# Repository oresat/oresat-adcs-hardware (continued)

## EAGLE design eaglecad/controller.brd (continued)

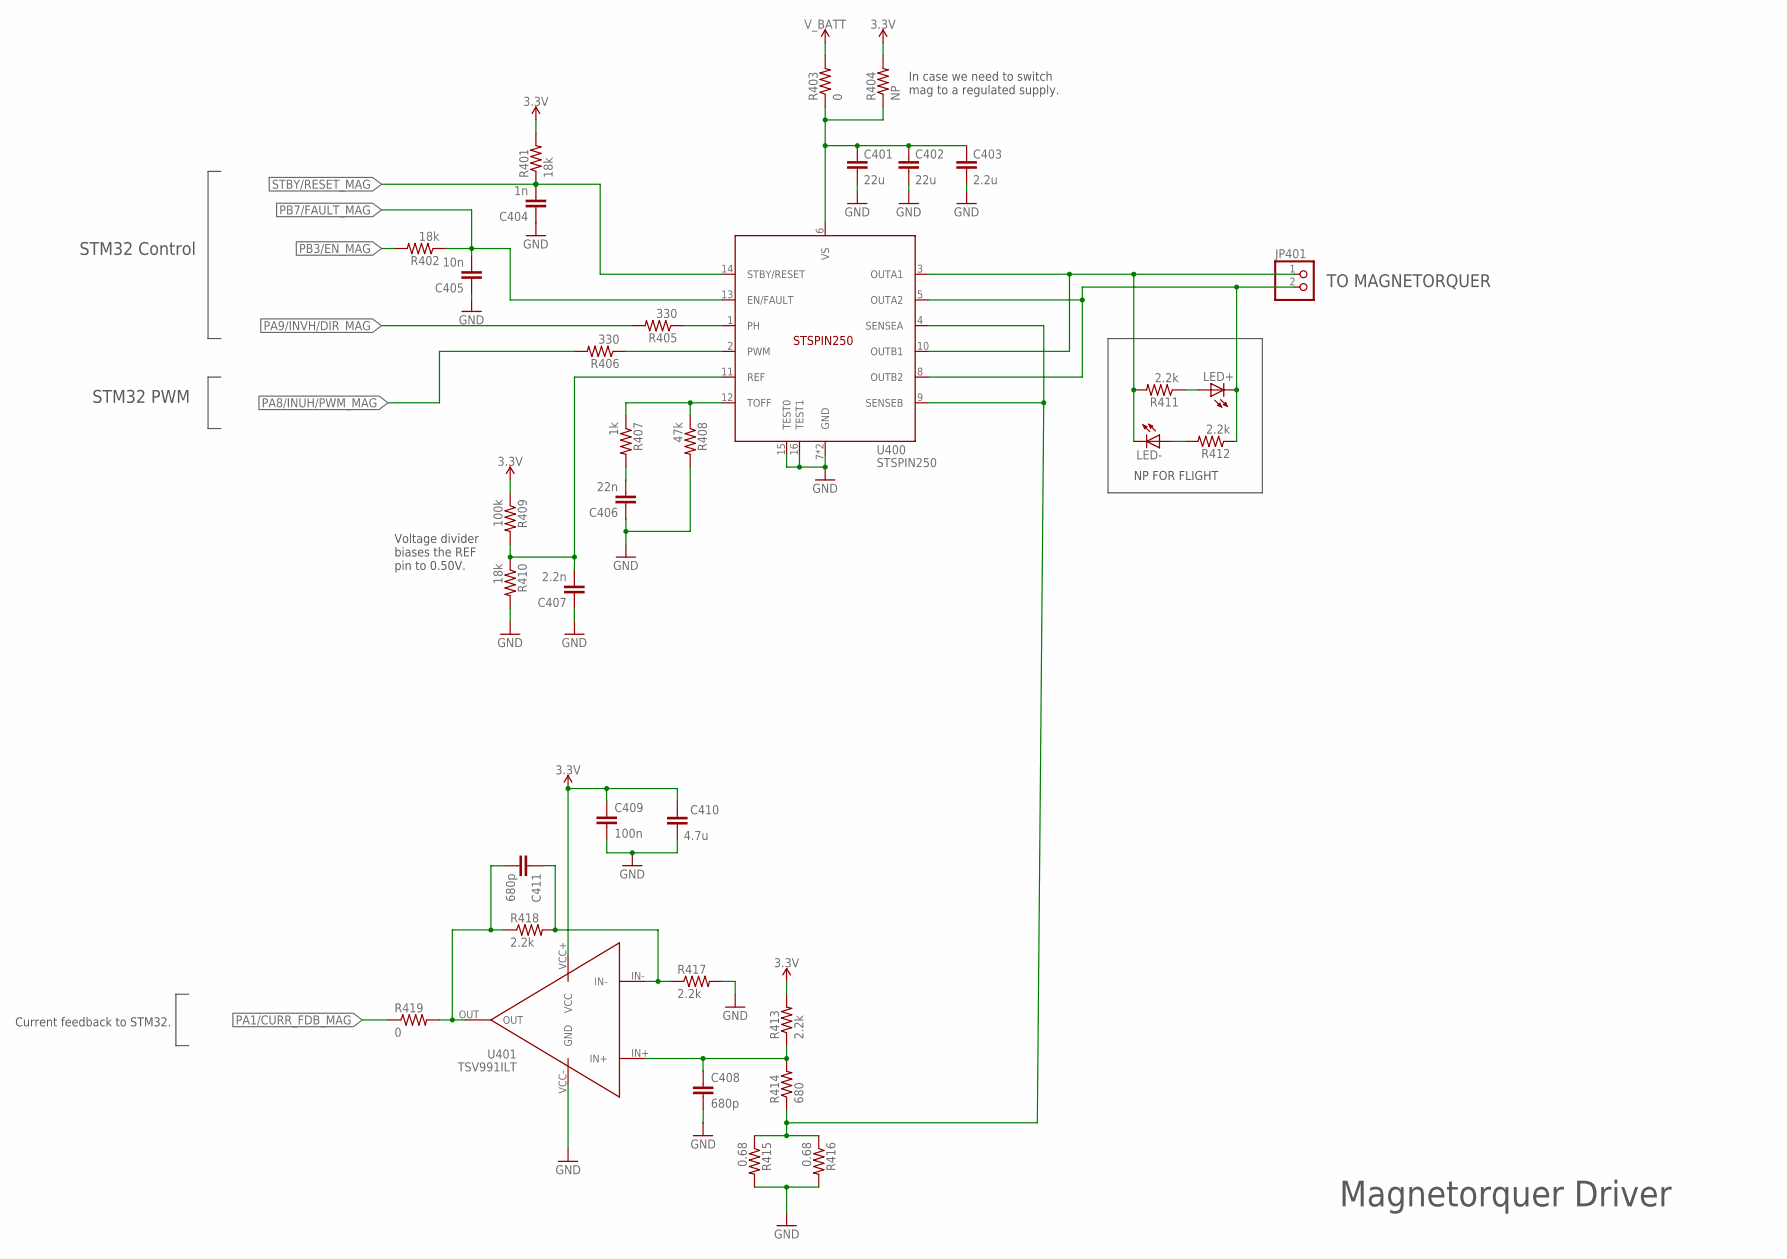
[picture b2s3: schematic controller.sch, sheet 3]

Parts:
C401, C402: 22u; .0603-B-NOSILK; MPN CL05B104KO5NNNC
C403: 2.2u; .0603-B-NOSILK; MPN CL05B104KO5NNNC
C404: 1n; .0402-B-NOSILK; MPN CL05B104KO5NNNC
C405: 10n; .0402-B-NOSILK; MPN CL05B104KO5NNNC
C406: 22n; .0402-B-NOSILK; MPN CL05B104KO5NNNC
C407: 2.2n; .0402-B-NOSILK; MPN CL05B104KO5NNNC
C408, C411: 680p; .0402-B-NOSILK; MPN CL05B104KO5NNNC
C409: 100n; .0402-B-NOSILK; MPN CL05B104KO5NNNC
C410: 4.7u; .0603-B-NOSILK; MPN CL05B104KO5NNNC
JP401: PINHD-1X2; 1X02
LED+: LEDCHIP-LED0603; CHIP-LED0603
LED-: LEDCHIP-LED0603; CHIP-LED0603
R401, R402, R410: 18k; .0402-B-NOSILK; MPN RC1005F6653CS
R403: 0; .0805-B-NOSILK
R404: NP; .0805-B-NOSILK
R405, R406: 330; .0402-B-NOSILK; MPN RC1005F6653CS
R407: 1k; .0402-B-NOSILK; MPN RC1005F6653CS
R408: 47k; .0402-B-NOSILK; MPN RC1005F6653CS
R409: 100k; .0402-B-NOSILK; MPN RC1005F6653CS
R411, R412: 2.2k; .0805-B-NOSILK
R413, R417, R418: 2.2k; .0402-B-NOSILK; MPN RC1005F6653CS
R414: 680; .0402-B-NOSILK; MPN RC1005F6653CS
R415, R416: 0.68; .0805-B-NOSILK
R419: 0; .0402-B-NOSILK; MPN RC1005F6653CS
U400: STSPIN250; VFQPN
U401: TSV991ILT; SOT23-5

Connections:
3.3V: C409.1, C410.1, R401.2, R404.2, R409.1, R413.2, U401.VCC+ (VCC); also elsewhere on the board
GND: C401.2, C402.2, C403.2, C404.1, C405.1, C406.1, C407.1, C408.2, C409.2, C410.2, R408.2, R410.2, R415.2, R416.2, R417.2, U400.7 (GND), U400.15 (TEST0), U400.16 (TEST1), U400.EPAD (GND), U401.VCC- (GND); also elsewhere on the board
unnamed: C406.2, R407.2
unnamed: R406.1, U400.2 (PWM)
unnamed: R405.1, U400.1 (PH)
unnamed: C408.1, R413.1, R414.2, U401.IN+
unnamed: C411.1, R417.1, R418.2, U401.IN-
unnamed: R407.1, R408.1, U400.12 (TOFF)
unnamed: C401.1, C402.1, C403.1, R403.1, R404.1, U400.6 (VS)
unnamed: LED+.A, R411.1
unnamed: LED-.A, R412.2
unnamed: C407.2, R409.2, R410.1, U400.11 (REF)
unnamed: C411.2, R418.1, R419.2, U401.OUT
OUT1: JP401.1, LED-.C, R411.2, U400.3 (OUTA1), U400.10 (OUTB1)
OUT2: JP401.2, LED+.C, R412.1, U400.5 (OUTA2), U400.8 (OUTB2)
PA1/CURR_FDB_MAG: R419.1; also elsewhere on the board
PA8/INUH/PWM_MAG: R406.2; also elsewhere on the board
PA9/INVH/DIR_MAG: R405.2; also elsewhere on the board
PB3/EN_MAG: R402.2; also elsewhere on the board
PB7/FAULT_MAG: C405.2, R402.1, U400.13 (EN/FAULT); also elsewhere on the board
SENSE_MAG: R414.1, R415.1, R416.1, U400.4 (SENSEA), U400.9 (SENSEB)
STBY/RESET_MAG: C404.2, R401.1, U400.14 (STBY/RESET)
V_BATT: R403.2; also elsewhere on the board

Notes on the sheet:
TO MAGNETORQUER
Magnetorquer Driver
Current feedback to STM32.
Voltage divider biases the REF pin to 0.50V.
NP FOR FLIGHT
STM32 PWM
STM32 Control
In case we need to switch mag to a regulated supply.

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
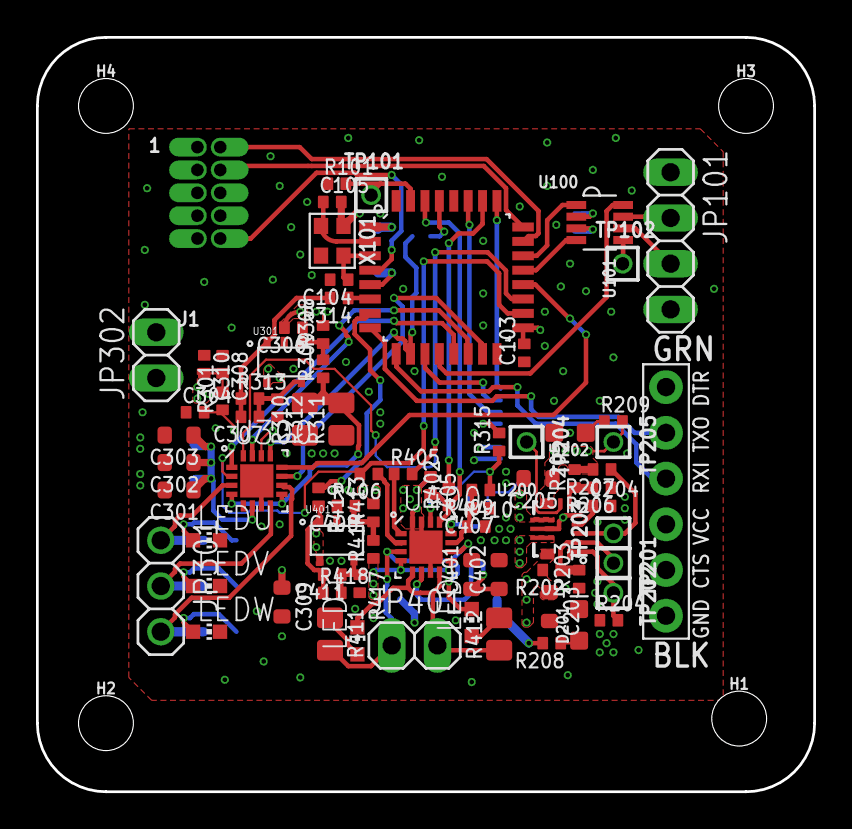
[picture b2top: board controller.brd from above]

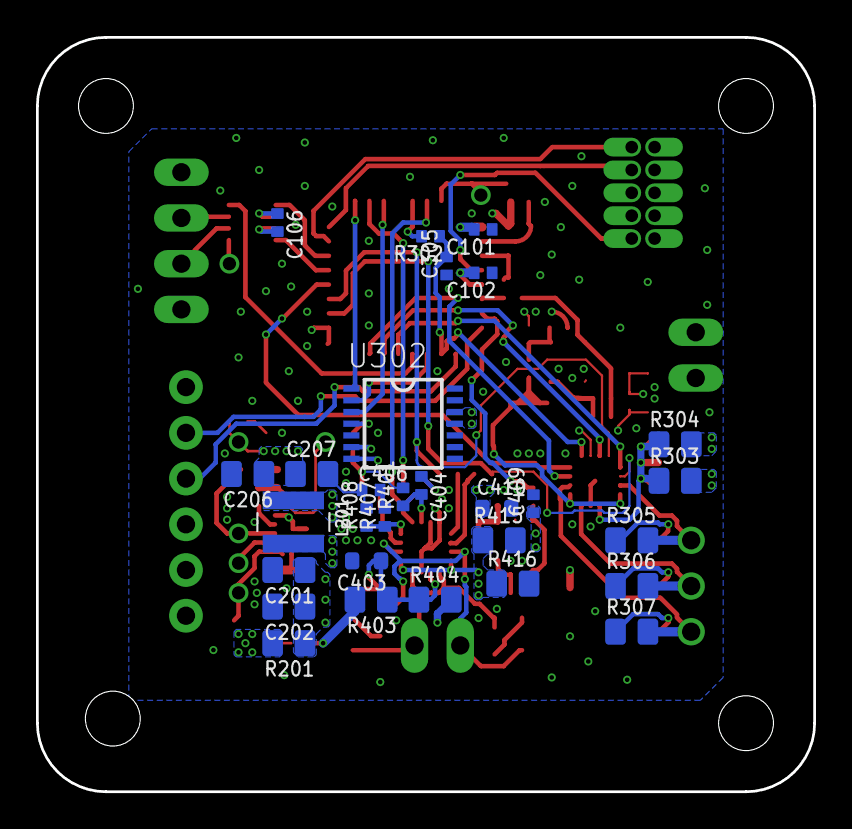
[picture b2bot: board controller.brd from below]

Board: 4 copper layers, 43.2 x 41.9 mm, 112 parts (29 on the bottom side), 73 nets.

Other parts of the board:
J1: 1.27MM-SWD-CONNECTOR; 1.27MM_2X5

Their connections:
NRESET: J1.!RESET; also elsewhere on the board
SWCLK: J1.SWDCLK; also elsewhere on the board
SWDIO: J1.SWDIO; also elsewhere on the board

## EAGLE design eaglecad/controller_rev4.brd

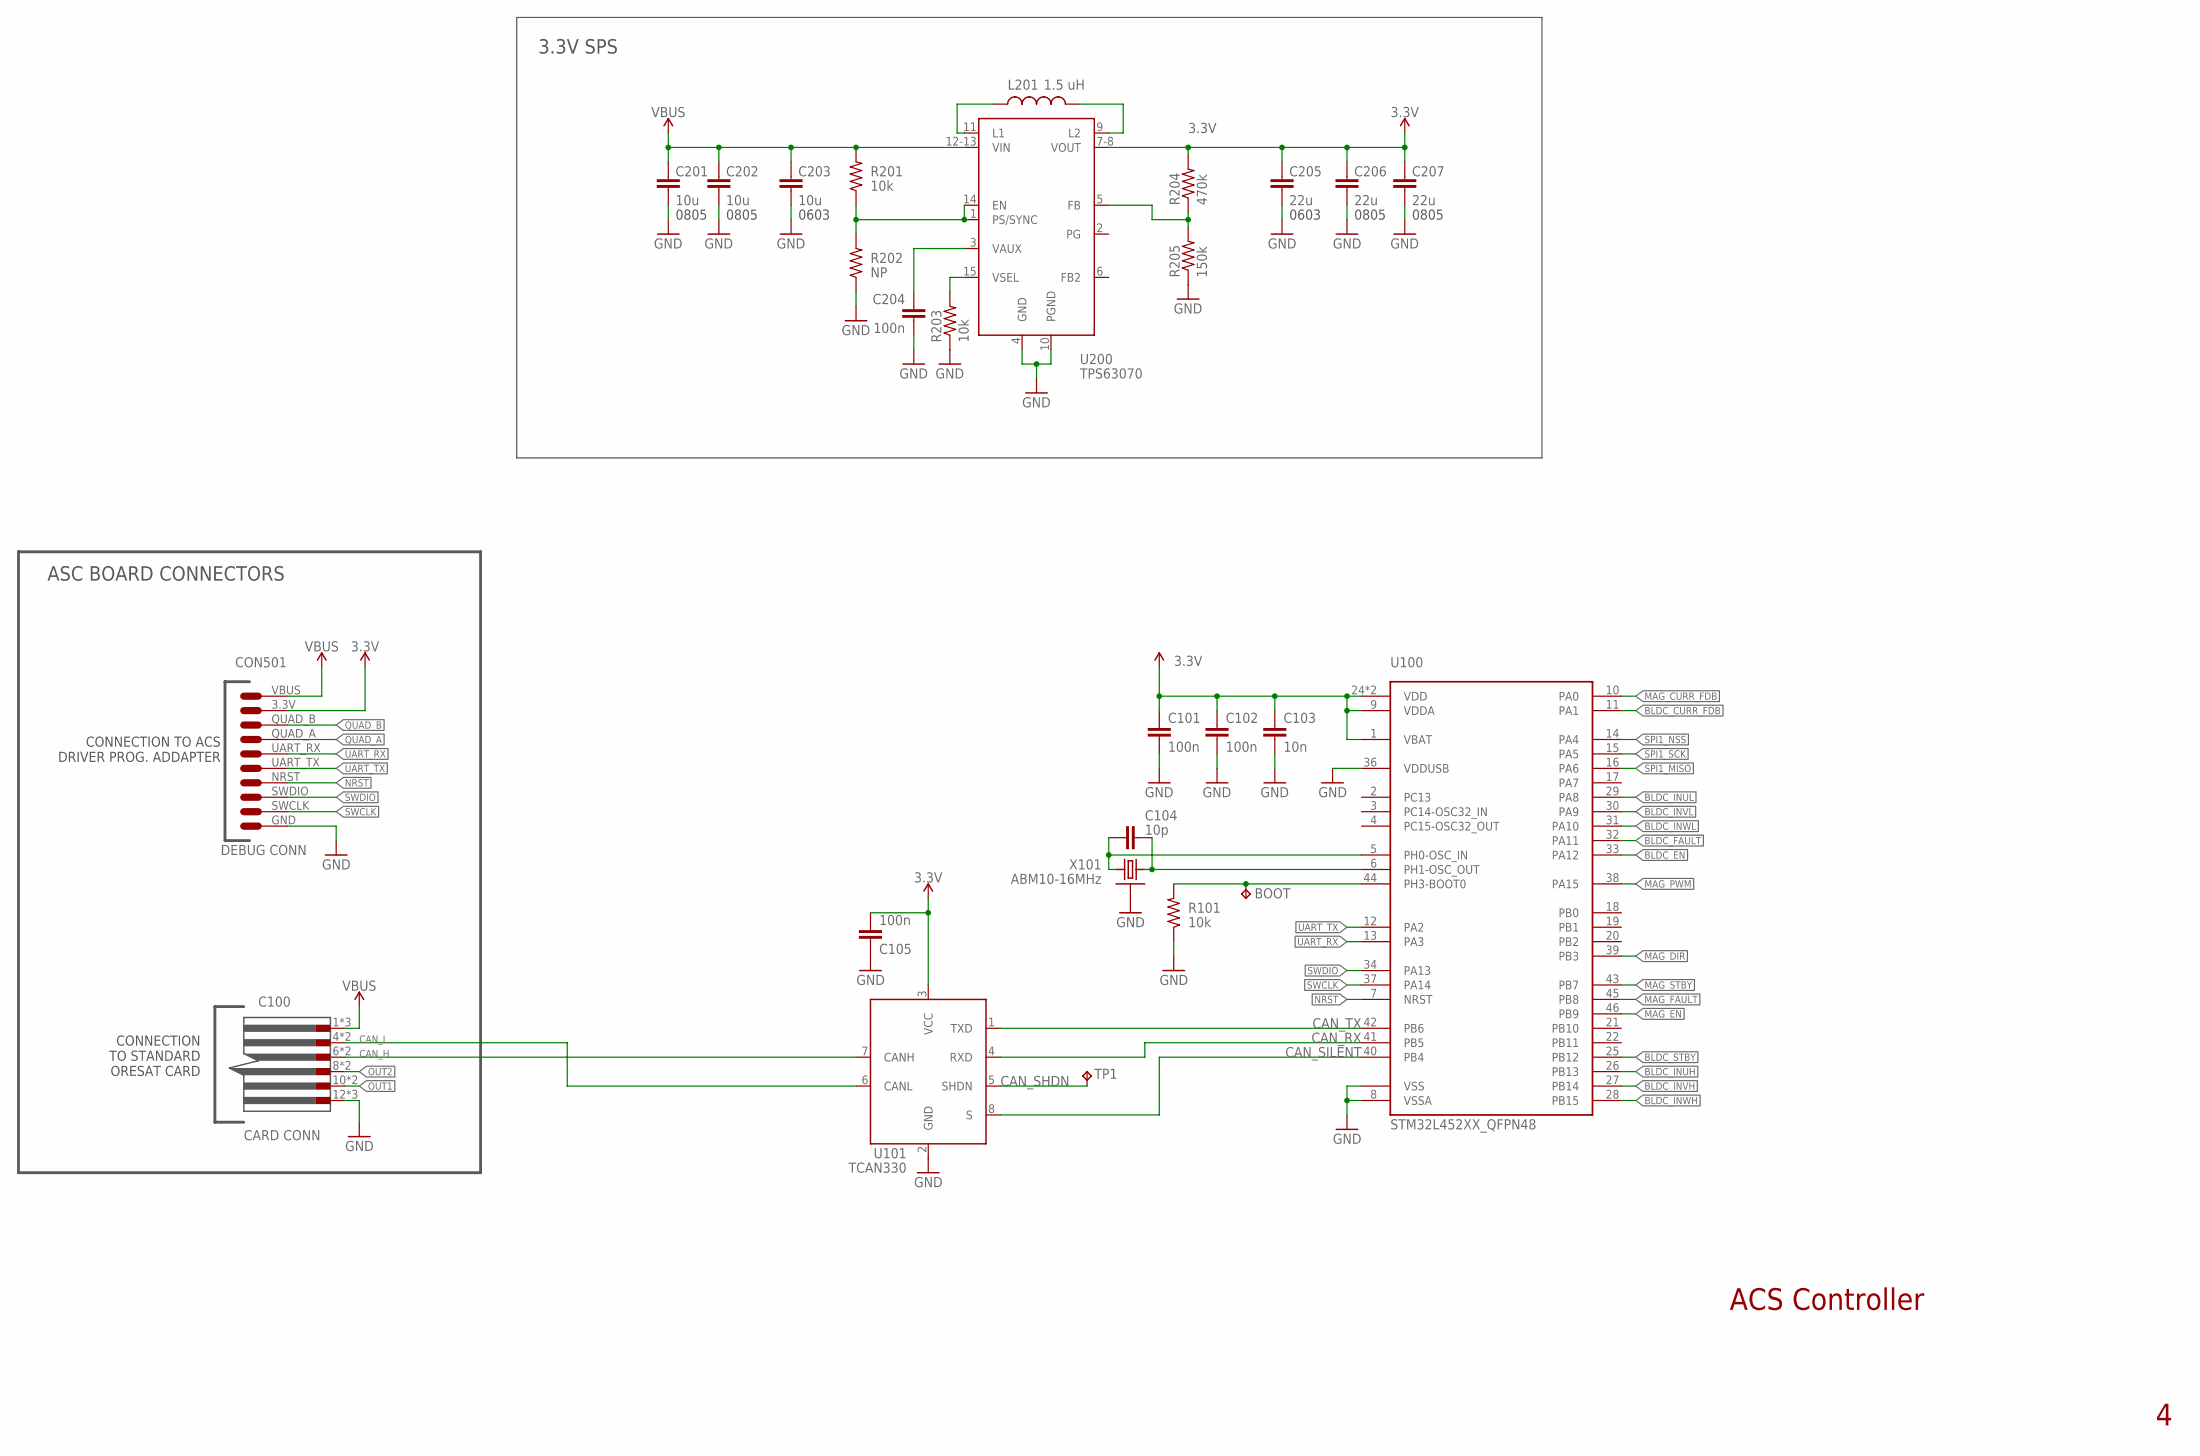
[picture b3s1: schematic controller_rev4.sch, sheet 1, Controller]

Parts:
BOOT: TPTP15SQ; TP15SQ
C100: CARD CONN; LOW-PROFILE_CONNECTOR(TAB)
C101, C102, C105, C204: 100n; .0402-B-NOSILK; MPN CL05B104KO5NNNC
C103: 10n; .0402-B-NOSILK; MPN CL05B104KO5NNNC
C104: 10p; .0402-B-NOSILK; MPN CL05C200JB51PNC
C201, C202: 10u; .0805-B-NOSILK
C203: 10u; .0603-B-NOSILK; MPN CL05B104KO5NNNC
C205: 22u; .0603-B-NOSILK; MPN CL05B104KO5NNNC
C206, C207: 22u; .0805-B-NOSILK
C501: DEBUG_CON
L201: 1.5 uH; L-COILCRAFT-XFL4020; MPN XFL4020-152ME
R101, R201, R203: 10k; .0402-B-NOSILK; MPN RC1005F6653CS
R202: NP; .0402-B-NOSILK; MPN RC1005F6653CS
R204: 470k; .0402-B-NOSILK; MPN RC1005F6653CS
R205: 150k; .0402-B-NOSILK; MPN RC1005F6653CS
TP1: TPTP06R; TP06R
U100: STM32L452XX_QFPN48; QFPN-48
U101: TCAN330; SOT23-8_TI-DCN; MPN TCAN330GDCNT
U200: TPS63070; TPS63070X; MPN TPS63070
X101: ABM10-16MHz; CRYSTAL_2.5X2; MPN ECS-160-10-36Q-ES-TR

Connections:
3.3V: C101.1, C102.1, C103.1, C105.2, C205.1, C206.1, C207.1, C501.3.3V (2), R204.2, U100.1 (VBAT), U100.9 (VDDA), U100.24 (VDD), U100.48 (VDD), U101.3 (VCC), U200.7-8 (VOUT); also elsewhere on the board
BLDC_CURR_FDB: U100.11 (PA1); also elsewhere on the board
BLDC_EN: U100.33 (PA12); also elsewhere on the board
BLDC_FAULT: U100.32 (PA11); also elsewhere on the board
BLDC_INUH: U100.26 (PB13); also elsewhere on the board
BLDC_INUL: U100.29 (PA8); also elsewhere on the board
BLDC_INVH: U100.27 (PB14); also elsewhere on the board
BLDC_INVL: U100.30 (PA9); also elsewhere on the board
BLDC_INWH: U100.28 (PB15); also elsewhere on the board
BLDC_INWL: U100.31 (PA10); also elsewhere on the board
BLDC_STBY: U100.25 (PB12); also elsewhere on the board
BOOT: BOOT.TP, R101.2, U100.44 (PH3-BOOT0)
CAN_H: C100.6 (3), U101.7 (CANH); also elsewhere on the board
CAN_L: C100.4 (2), U101.6 (CANL); also elsewhere on the board
CAN_RX: U100.41 (PB5), U101.4 (RXD)
CAN_SHDN: TP1.TP, U101.5 (SHDN)
CAN_SILENT: U100.40 (PB4), U101.8 (S)
CAN_TX: U100.42 (PB6), U101.1 (TXD)
CLK1: C104.1, U100.5 (PH0-OSC_IN), X101.3 (2)
CLK2: C104.2, U100.6 (PH1-OSC_OUT), X101.1
GND: C100.12 (6), C101.2, C102.2, C103.2, C105.1, C201.2, C202.2, C203.2, C204.2, C205.2, C206.2, C207.2, C501.GND (10), R101.1, R202.1, R203.1, R205.1, U100.8 (VSSA), U100.23 (VSS), U100.35 (VSS), U100.36 (VDDUSB), U100.47 (VSS), U100.EPAD (VSS), U101.2 (GND), U200.4 (GND), U200.10 (PGND), X101.2 (SHIELD), X101.4 (SHIELD); also elsewhere on the board
MAG_CURR_FDB: U100.10 (PA0); also elsewhere on the board
MAG_DIR: U100.39 (PB3); also elsewhere on the board
MAG_EN: U100.46 (PB9); also elsewhere on the board
MAG_FAULT: U100.45 (PB8); also elsewhere on the board
MAG_PWM: U100.38 (PA15); also elsewhere on the board
MAG_STBY: U100.43 (PB7); also elsewhere on the board
NRST: C501.NRST (7), U100.7 (NRST)
QUAD_A: C501.QUAD_A (4); also elsewhere on the board
QUAD_B: C501.QUAD_B (3); also elsewhere on the board
SPI1_MISO: U100.16 (PA6); also elsewhere on the board
SPI1_NSS: U100.14 (PA4); also elsewhere on the board
SPI1_SCK: U100.15 (PA5); also elsewhere on the board
SWCLK: C501.SWCLK (9), U100.37 (PA14)
SWDIO: C501.SWDIO (8), U100.34 (PA13)
TPS-EN2: R201.1, R202.2, U200.1 (PS/SYNC), U200.14 (EN)
TPS-FB2: R204.1, R205.2, U200.5 (FB)
TPS-L5: L201.1, U200.11 (L1)
TPS-L6: L201.2, U200.9 (L2)
TPS-VAUX2: C204.1, U200.3 (VAUX)
TPS-VSEL2: R203.2, U200.15 (VSEL)
UART_RX: C501.UART_RX (5), U100.13 (PA3)
UART_TX: C501.UART_TX (6), U100.12 (PA2)
VBUS: C100.1, C201.1, C202.1, C203.1, R201.2, U200.12-13 (VIN); also elsewhere on the board
V_BATT: C501.VBUS (1)

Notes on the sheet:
ACS Controller
3.3V SPS
0603
0805
CONNECTION TO ACS DRIVER PROG. ADDAPTER
CONNECTION TO STANDARD ORESAT CARD
ASC BOARD CONNECTORS
CON501
DEBUG CONN

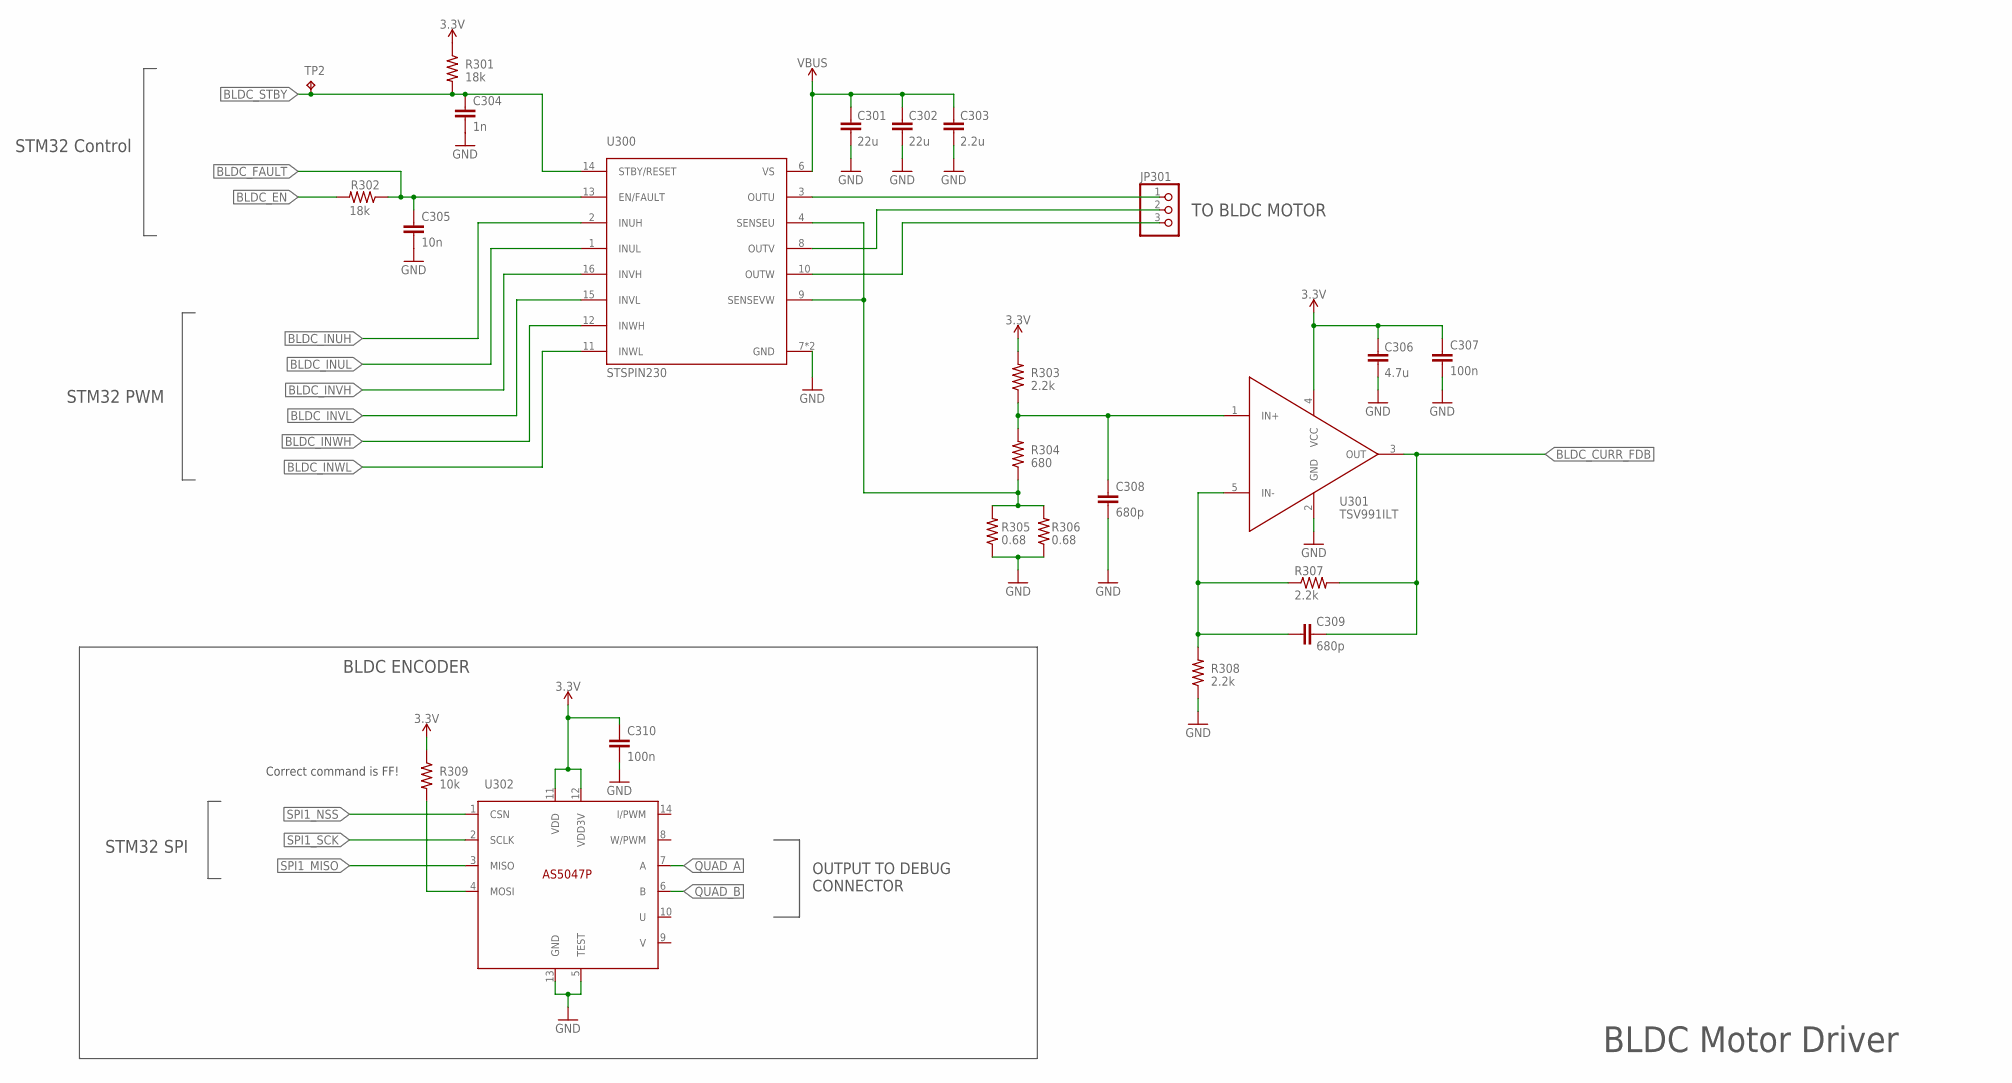
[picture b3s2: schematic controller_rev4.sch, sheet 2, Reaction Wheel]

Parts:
C301, C302: 22u; .0603-B-NOSILK; MPN CL05B104KO5NNNC
C303: 2.2u; .0603-B-NOSILK; MPN CL05B104KO5NNNC
C304: 1n; .0402-B-NOSILK; MPN CL05B104KO5NNNC
C305: 10n; .0402-B-NOSILK; MPN CL05B104KO5NNNC
C306: 4.7u; .0603-B-NOSILK; MPN CL05B104KO5NNNC
C307, C310: 100n; .0402-B-NOSILK; MPN CL05B104KO5NNNC
C308, C309: 680p; .0402-B-NOSILK; MPN CL05B104KO5NNNC
JP301: PINHD-1X03_2.00; 1X03M
R301, R302: 18k; .0402-B-NOSILK; MPN RC1005F6653CS
R303, R307, R308: 2.2k; .0402-B-NOSILK; MPN RC1005F6653CS
R304: 680; .0402-B-NOSILK; MPN RC1005F6653CS
R305, R306: 0.68; .0805-B-NOSILK
R309: 10k; .0402-B-NOSILK; MPN RC1005F6653CS
TP2: TPTP06R; TP06R
U300: STSPIN230; VFQPN
U301: TSV991ILT; SOT23-5
U302: AS5047P; TSSOP14

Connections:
3.3V: C306.1, C307.1, C310.1, R301.1, R303.2, R309.1, U301.4 (VCC), U302.11 (VDD), U302.12 (VDD3V); also elsewhere on the board
AS5047_MOSI: R309.2, U302.4 (MOSI)
BLDC_CURR_FDB: C309.1, R307.2, U301.3 (OUT); also elsewhere on the board
BLDC_EN: R302.2; also elsewhere on the board
BLDC_FAULT: C305.1, R302.1, U300.13 (EN/FAULT); also elsewhere on the board
BLDC_INUH: U300.2 (INUH); also elsewhere on the board
BLDC_INUL: U300.1 (INUL); also elsewhere on the board
BLDC_INVH: U300.16 (INVH); also elsewhere on the board
BLDC_INVL: U300.15 (INVL); also elsewhere on the board
BLDC_INWH: U300.12 (INWH); also elsewhere on the board
BLDC_INWL: U300.11 (INWL); also elsewhere on the board
BLDC_STBY: C304.1, R301.2, TP2.TP, U300.14 (STBY/RESET); also elsewhere on the board
B_IN+: C308.1, R303.1, R304.2, U301.1 (IN+)
B_IN-: C309.2, R307.1, R308.2, U301.5 (IN-)
GND: C301.2, C302.2, C303.2, C304.2, C305.2, C306.2, C307.2, C308.2, C310.2, R305.1, R306.1, R308.1, U300.7 (GND), U300.EPAD (GND), U301.2 (GND), U302.5 (TEST), U302.13 (GND); also elsewhere on the board
QUAD_A: U302.7 (A); also elsewhere on the board
QUAD_B: U302.6 (B); also elsewhere on the board
SENSE_BLDC: R304.1, R305.2, R306.2, U300.4 (SENSEU), U300.9 (SENSEVW)
SPI1_MISO: U302.3 (MISO); also elsewhere on the board
SPI1_NSS: U302.1 (CSN); also elsewhere on the board
SPI1_SCK: U302.2 (SCLK); also elsewhere on the board
U: JP301.1, U300.3 (OUTU)
V: JP301.2, U300.8 (OUTV)
VBUS: C301.1, C302.1, C303.1, U300.6 (VS); also elsewhere on the board
W: JP301.3, U300.10 (OUTW)

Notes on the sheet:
TO BLDC MOTOR
BLDC Motor Driver
STM32 PWM
STM32 Control
Correct command is FF!
STM32 SPI
BLDC ENCODER
OUTPUT TO DEBUG CONNECTOR

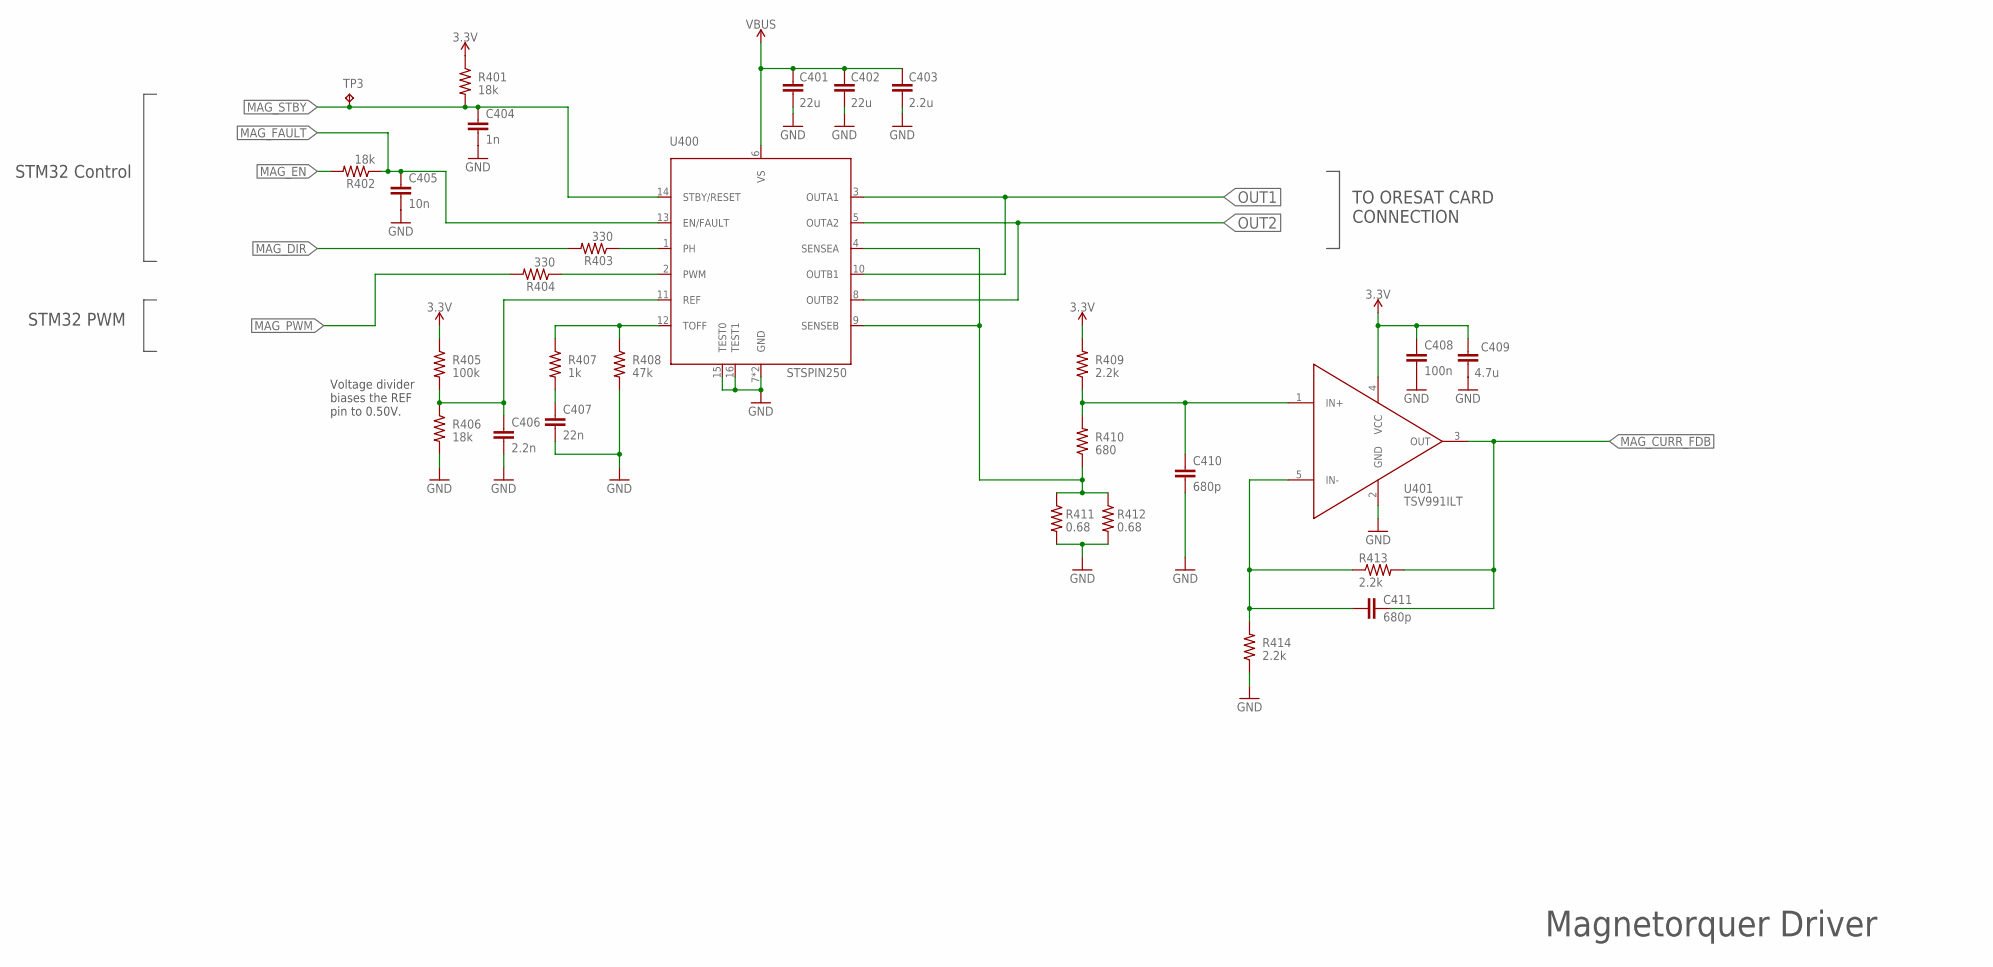
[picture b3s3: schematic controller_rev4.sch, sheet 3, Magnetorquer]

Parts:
C401, C402: 22u; .0603-B-NOSILK; MPN CL05B104KO5NNNC
C403: 2.2u; .0603-B-NOSILK; MPN CL05B104KO5NNNC
C404: 1n; .0402-B-NOSILK; MPN CL05B104KO5NNNC
C405: 10n; .0402-B-NOSILK; MPN CL05B104KO5NNNC
C406: 2.2n; .0402-B-NOSILK; MPN CL05B104KO5NNNC
C407: 22n; .0402-B-NOSILK; MPN CL05B104KO5NNNC
C408: 100n; .0402-B-NOSILK; MPN CL05B104KO5NNNC
C409: 4.7u; .0603-B-NOSILK; MPN CL05B104KO5NNNC
C410, C411: 680p; .0402-B-NOSILK; MPN CL05B104KO5NNNC
R401, R402, R406: 18k; .0402-B-NOSILK; MPN RC1005F6653CS
R403, R404: 330; .0402-B-NOSILK; MPN RC1005F6653CS
R405: 100k; .0402-B-NOSILK; MPN RC1005F6653CS
R407: 1k; .0402-B-NOSILK; MPN RC1005F6653CS
R408: 47k; .0402-B-NOSILK; MPN RC1005F6653CS
R409, R413, R414: 2.2k; .0402-B-NOSILK; MPN RC1005F6653CS
R410: 680; .0402-B-NOSILK; MPN RC1005F6653CS
R411, R412: 0.68; .0805-B-NOSILK
TP3: TPTP06R; TP06R
U400: STSPIN250; VFQPN
U401: TSV991ILT; SOT23-5

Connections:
3.3V: C408.1, C409.1, R401.1, R405.1, R409.2, U401.4 (VCC); also elsewhere on the board
250_REF: C406.1, R405.2, R406.1, U400.11 (REF)
250_TOFF: R407.1, R408.1, U400.12 (TOFF)
GND: C401.2, C402.2, C403.2, C404.2, C405.2, C406.2, C407.2, C408.2, C409.2, C410.2, R406.2, R408.2, R411.2, R412.2, R414.1, U400.7 (GND), U400.15 (TEST0), U400.16 (TEST1), U400.EPAD (GND), U401.2 (GND); also elsewhere on the board
MAG_CURR_FDB: C411.1, R413.2, U401.3 (OUT); also elsewhere on the board
MAG_DIR: R403.2; also elsewhere on the board
MAG_EN: R402.2; also elsewhere on the board
MAG_FAULT: C405.1, R402.1, U400.13 (EN/FAULT); also elsewhere on the board
MAG_PWM: R404.2; also elsewhere on the board
MAG_STBY: C404.1, R401.2, TP3.TP, U400.14 (STBY/RESET); also elsewhere on the board
M_IN+: C410.1, R409.1, R410.2, U401.1 (IN+)
M_IN-: C411.2, R413.1, R414.2, U401.5 (IN-)
M_PH: R403.1, U400.1 (PH)
M_PWM: R404.1, U400.2 (PWM)
OUT1: U400.3 (OUTA1), U400.10 (OUTB1); also elsewhere on the board
OUT2: U400.5 (OUTA2), U400.8 (OUTB2); also elsewhere on the board
SENSE_MAG: R410.1, R411.1, R412.1, U400.4 (SENSEA), U400.9 (SENSEB)
TOFF1: C407.1, R407.2
VBUS: C401.1, C402.1, C403.1, U400.6 (VS); also elsewhere on the board

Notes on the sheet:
TO ORESAT CARD CONNECTION
Magnetorquer Driver
Voltage divider biases the REF pin to 0.50V.
STM32 PWM
STM32 Control

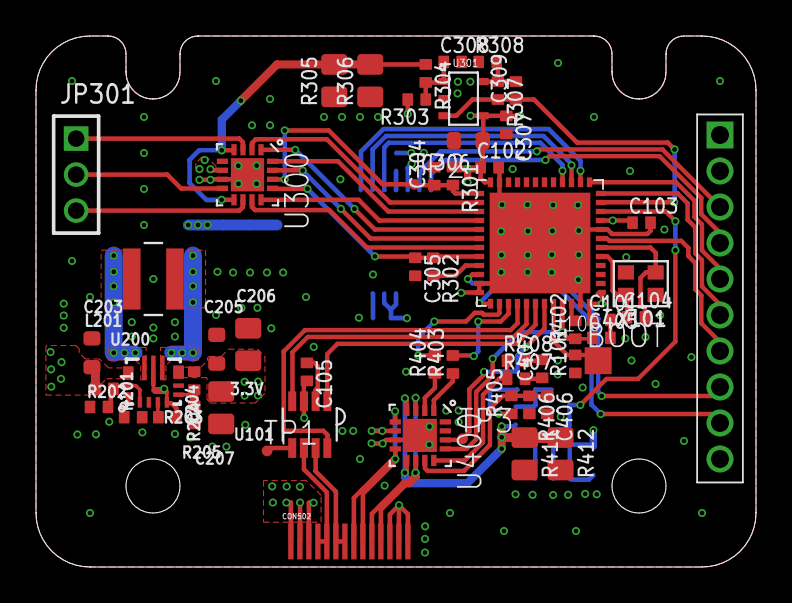
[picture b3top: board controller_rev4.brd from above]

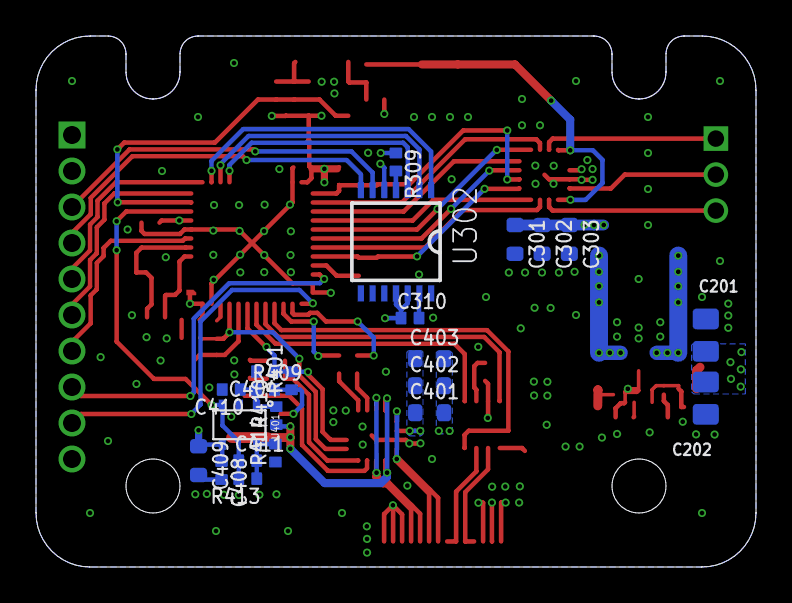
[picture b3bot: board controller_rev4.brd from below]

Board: 4 copper layers, 40.0 x 29.5 mm, 79 parts (22 on the bottom side), 61 nets.

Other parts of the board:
CON502: CARD CONN; LOW-PROFILE_CONNECTOR(TAB)

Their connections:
CAN_H: CON502.6, CON502.7; also elsewhere on the board
CAN_L: CON502.4, CON502.5; also elsewhere on the board
GND: CON502.12, CON502.13, CON502.14; also elsewhere on the board
OUT1: CON502.10, CON502.11; also elsewhere on the board
OUT2: CON502.8, CON502.9; also elsewhere on the board
VBUS: CON502.1, CON502.2, CON502.3; also elsewhere on the board
